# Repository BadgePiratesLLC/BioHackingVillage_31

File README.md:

# Project-Galadriel

Biohack village - 2023
Project Link - https://badgepirates.atlassian.net/jira/software/c/projects/BHV23/boards/21

Meeting 1/30/2023 - fg, Networkgeek, lee
 - Discussed
   - Showed Example
   - Ordered some lenses for testing

Meeting 2/2/2023 - fg, Networkgeek, nina, lee
  - Discussed 
    - High tech vs low Tech
    - fg to make a POC with ESP32 and Camera
    - May need to 3d print Lense mount
    - If possible plan for Low tech version
    - Would like TFT Display but also investigate Webpage from Badge of Camera view
    - Look for a Hot or Not on Slide images
    - Kit to assemble or to include the badge in would be cool - nina
    - 5k Budget - 100 --> 150 
    
- UV LED - https://www.mouser.com/ProductDetail/Bivar/SM0603UV-400?qs=pceeu5JH%2FH%2FbOvJT9BLFMw%3D%3D
- ST3T Switch - https://www.digikey.com/en/products/detail/c-k/PCM13SMTR/1640113

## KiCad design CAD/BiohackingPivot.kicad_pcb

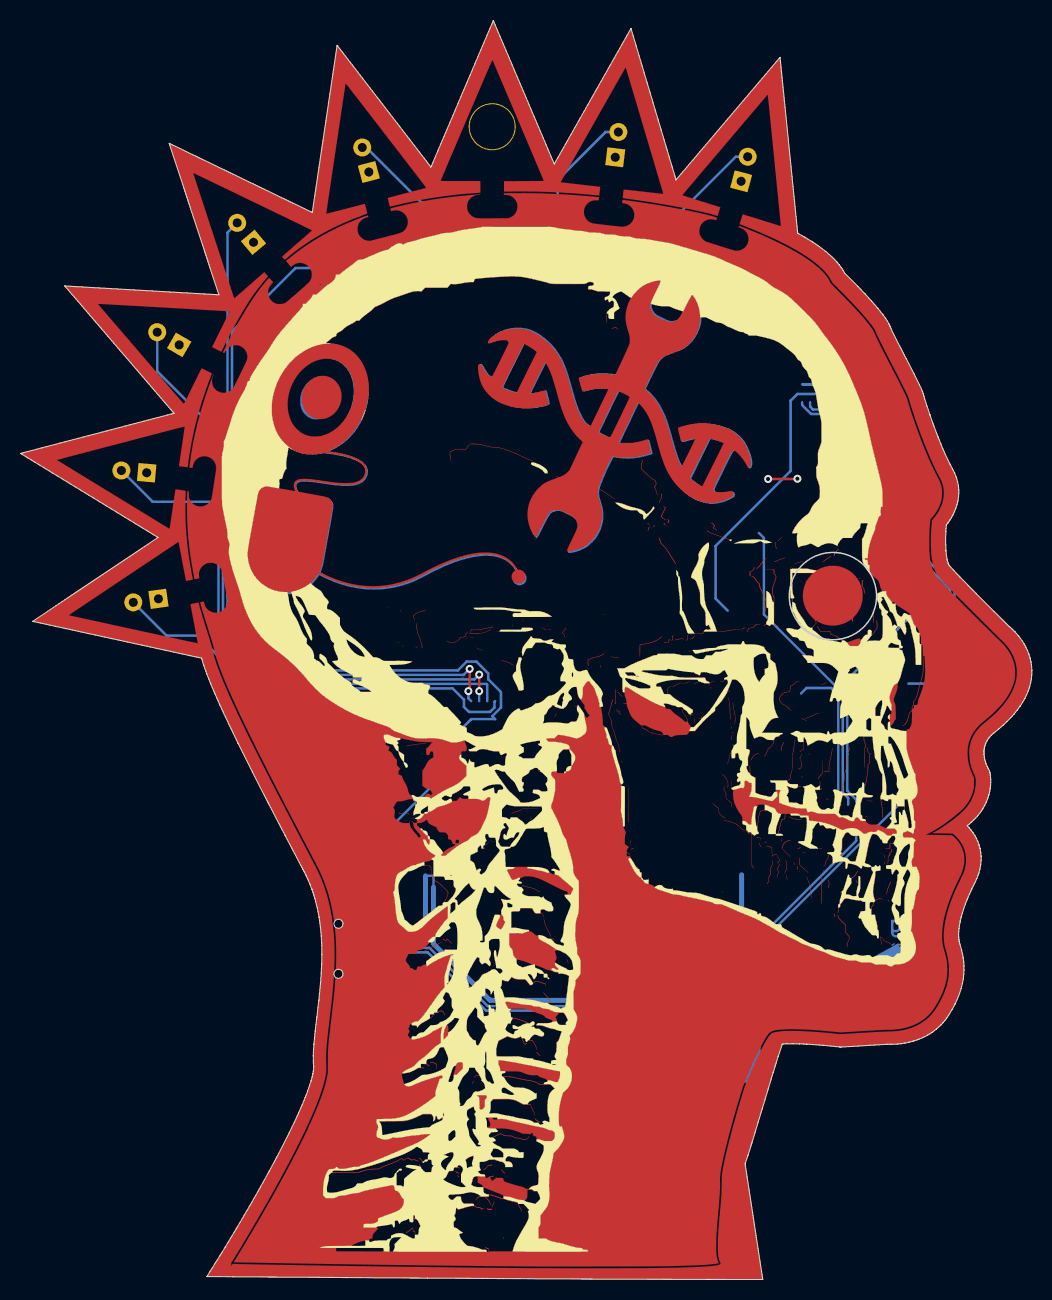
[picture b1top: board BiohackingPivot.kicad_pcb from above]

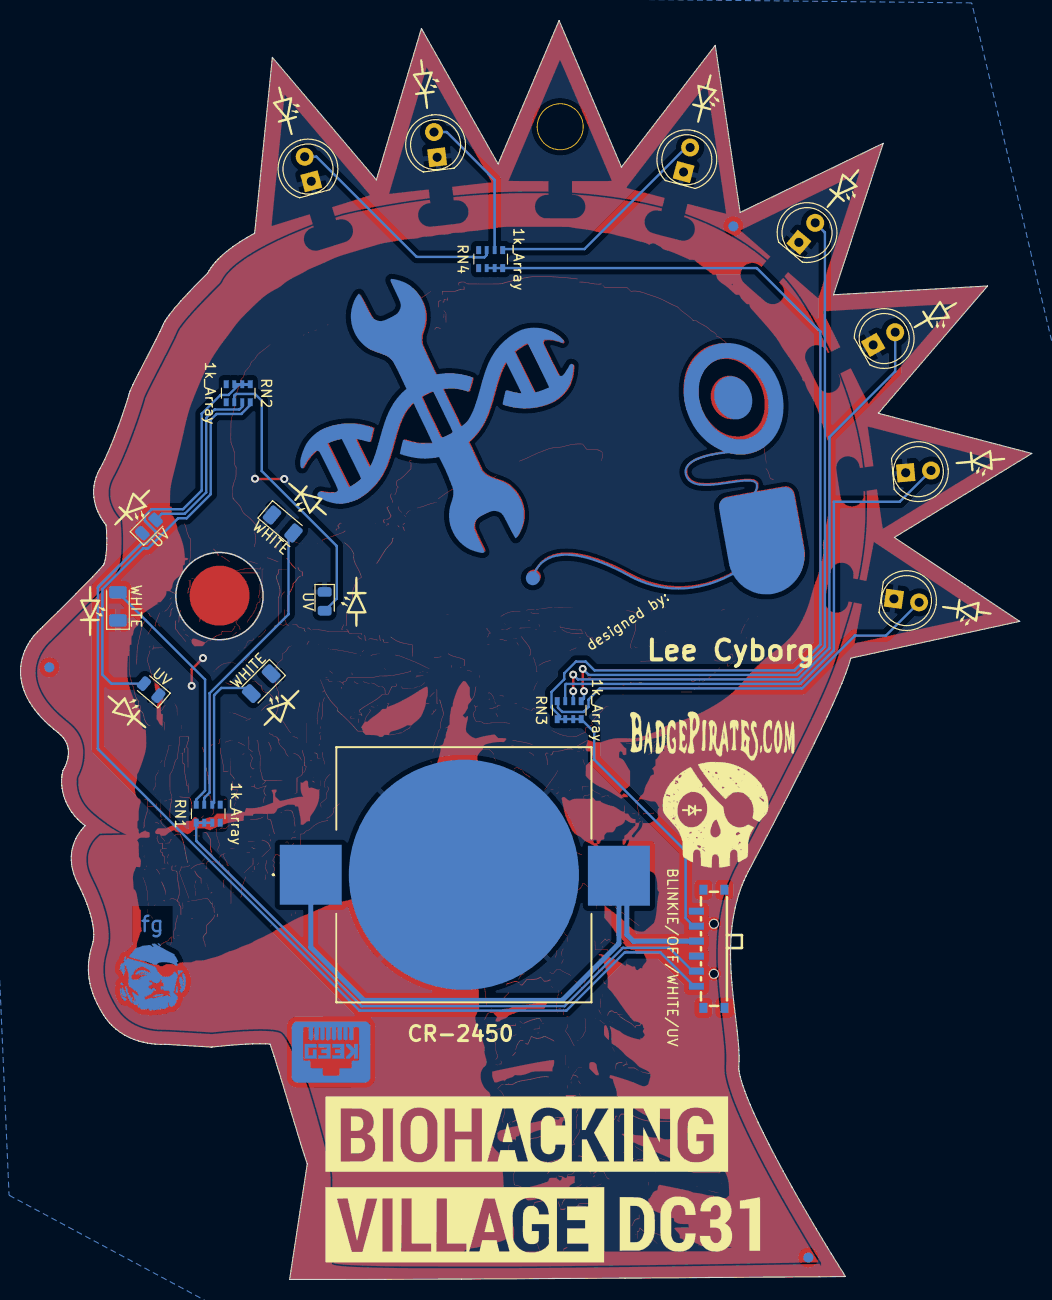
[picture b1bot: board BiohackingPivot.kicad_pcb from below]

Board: 2 copper layers, 101.1 x 125.8 mm, 19 parts (19 on the bottom side), 18 nets.

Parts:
BT1: Battery_Cell; BATHLD006SMT - CR2450
D1, D2, D3: UV; LED_0805_2012Metric
D4, D5, D6: WHITE; LED_1206_3216Metric
D7, D8, D9, D10, D11, D12, D13: LED; LED_D5.0mm
RN1, RN2, RN3, RN4: 1k_Array; R_Array_Convex_4x0603
SW3: SW-SP4T; SP4T - CUS-14TB

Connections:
+3.3V: BT1.1 (+), SW3.4
BLINKIE: RN3.1 (R1.1), RN3.2 (R2.1), RN3.3 (R3.1), RN3.4 (R4.1), RN4.2 (R2.1), RN4.3 (R3.1), RN4.4 (R4.1), SW3.5
GND: BT1.2 (-), D1.1 (K), D2.1 (K), D3.1 (K), D4.1 (K), D5.1 (K), D6.1 (K), D7.1 (K), D8.1 (K), D9.1 (K), D10.1 (K), D11.1 (K), D12.1 (K), D13.1 (K)
unnamed: D1.2 (A), RN2.6 (R3.2)
unnamed: D2.2 (A), RN2.7 (R2.2)
unnamed: D3.2 (A), RN2.8 (R1.2)
unnamed: D4.2 (A), RN1.6 (R3.2)
unnamed: D5.2 (A), RN1.7 (R2.2)
unnamed: D6.2 (A), RN1.8 (R1.2)
unnamed: D7.2 (A), RN3.5 (R4.2)
unnamed: D8.2 (A), RN3.6 (R3.2)
unnamed: D9.2 (A), RN3.7 (R2.2)
unnamed: D10.2 (A), RN3.8 (R1.2)
unnamed: D11.2 (A), RN4.5 (R4.2)
unnamed: D12.2 (A), RN4.6 (R3.2)
unnamed: D13.2 (A), RN4.7 (R2.2)
UV: RN2.1 (R1.1), RN2.2 (R2.1), RN2.3 (R3.1), SW3.1
WHITE: RN1.1 (R1.1), RN1.2 (R2.1), RN1.3 (R3.1), SW3.2

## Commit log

2023-05-14 schematic and Layout
2023-06-08 Add artwork
2023-06-12 Inital Artwork Take
2023-06-13 Updated artwork to final review
2023-06-13 Artwork
2023-06-13 Flipped back artwork
2023-06-15 Cleaned up CAD-Export
2023-06-15 Removed extra parts from Artwork file
2023-06-15 Finalizing Proto
2023-06-24 alt layout
2023-07-09 fixes
2023-07-09 Cleaning up folder and page settings
2023-07-18 gerbers
